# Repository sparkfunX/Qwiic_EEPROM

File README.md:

Qwiic EEPROM - 512Kbit
=======================================

[*Qwiic EEPROM - 512Kbit (SPX-14764)*](https://www.sparkfun.com/products/14764)

A simple breakout for the 512kbit common I2C EEPROMs.

Repository Contents
-------------------

* **/Hardware** - Eagle design files (.brd, .sch)
* **/Firmware** - EEPROM test sketch

Documentation
------------

* **[SparkFun External EEPROM Arduino Library](https://github.com/sparkfun/SparkFun_External_EEPROM_Arduino_Library)** - Arduino library for the Qwiic EEPROM - 512Kbit
* **[Datasheet CAT24C512](https://www.onsemi.com/pub/Collateral/CAT24C512-D.PDF)** - Datasheet for EEPROM part number 24512A
* **[Datasheet RM24C512C](https://cdn.sparkfun.com/assets/2/c/4/c/0/DS-RM24C512C_082.pdf)** - Datasheet for EEPROM part number 24512C
* **[Reading and Writing Serial EEPROMs](https://learn.sparkfun.com/tutorials/reading-and-writing-serial-eeproms)** - Tutorial  

License Information
-------------------

This product is _**open source**_! 

Please review the LICENSE.md file for license information. 

If you have any questions or concerns on licensing, please contact technical support on our [SparkFun forums](https://forum.sparkfun.com/viewforum.php?f=152).

Distributed as-is; no warranty is given.

- Your friends at SparkFun.

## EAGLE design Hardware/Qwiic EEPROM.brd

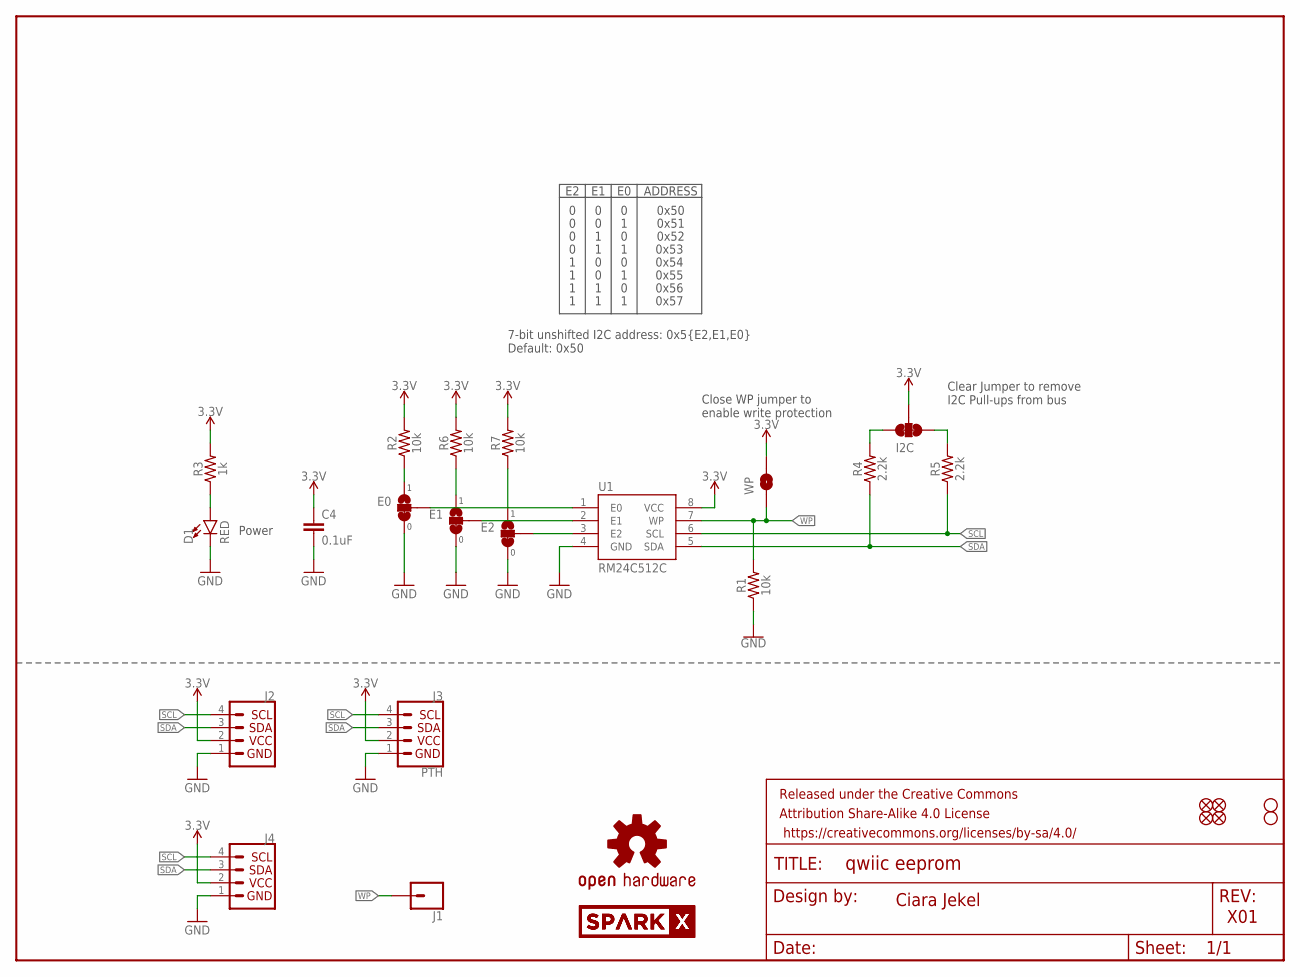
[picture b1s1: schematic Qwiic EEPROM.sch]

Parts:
C4: 0.1uF; 0603
D1: RED; LED-0603
E0, E1, E2: JUMPER-SMT_3_1-NC_TRACE_SILK; SMT-JUMPER_3_1-NC_TRACE_SILK
FRAME1: FRAME-LETTER; CREATIVE_COMMONS
I2C: JUMPER-SMT_3_2-NC_TRACE_SILK; SMT-JUMPER_3_2-NC_TRACE_SILK
J1: CONN_01PTH_NO_SILK_YES_STOP; 1X01_NO_SILK
J2, J4: QWIIC_CONNECTORJS-1MM; 1X04_1MM_RA
J3: PTH; 1X04_NO_SILK
JP1, JP2, JP5, JP6: FIDUCIALUFIDUCIAL; MICRO-FIDUCIAL
JP3, JP4: STAND-OFF
LOGO1: OSHW-LOGOMINI; OSHW-LOGO-MINI
R1, R2, R6, R7: 10k; 0603
R3: 1k; 0603
R4, R5: 2.2k; 0603
U1: RM24C512C; SO08
U$1, U$2: SPARKX-LOGO4; SPARKX-MEDIUM
WP: JUMPER-SMT_2_NO_SILK; SMT-JUMPER_2_NO_SILK

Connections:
3.3V: C4.1, I2C.2, J2.2, J3.2 (VCC), J4.2, R2.2, R3.2, R6.2, R7.2, U1.8 (VCC), WP.2
GND: C4.2, D1.C, E0.3, E1.3, E2.3, J2.1, J3.1 (GND), J4.1, R1.1, U1.4 (GND)
unnamed: I2C.1, R5.2
unnamed: I2C.3, R4.2
unnamed: D1.A, R3.1
unnamed: E2.2, U1.3 (E2)
unnamed: E1.2, U1.2 (E1)
unnamed: E0.2, U1.1 (E0)
unnamed: E0.1, R2.1
unnamed: E2.1, R7.1
unnamed: E1.1, R6.1
SCL: J2.4, J3.4 (SCL), J4.4, R5.1, U1.6 (SCL)
SDA: J2.3, J3.3 (SDA), J4.3, R4.1, U1.5 (SDA)
WP: J1.1, R1.2, U1.7 (WP), WP.1

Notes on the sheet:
Ciara Jekel
X01
7-bit unshifted I2C address: 0x5{E2,E1,E0} Default: 0x50
Clear Jumper to remove I2C Pull-ups from bus
Power
Close WP jumper to enable write protection
ADDRESS
0x50
0x51
0x52
0x53
0x54
0x55
0x56
0x57

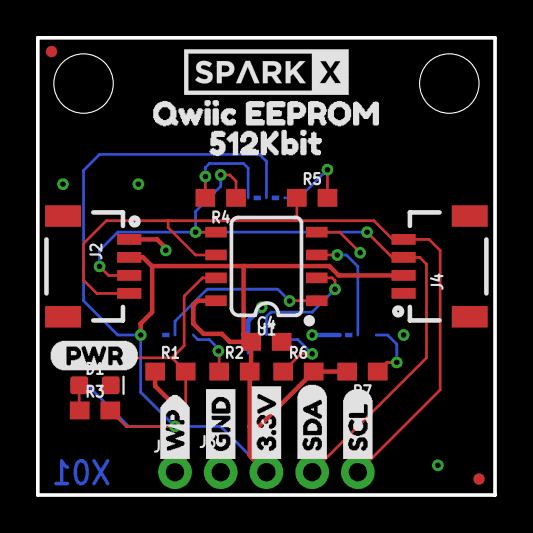
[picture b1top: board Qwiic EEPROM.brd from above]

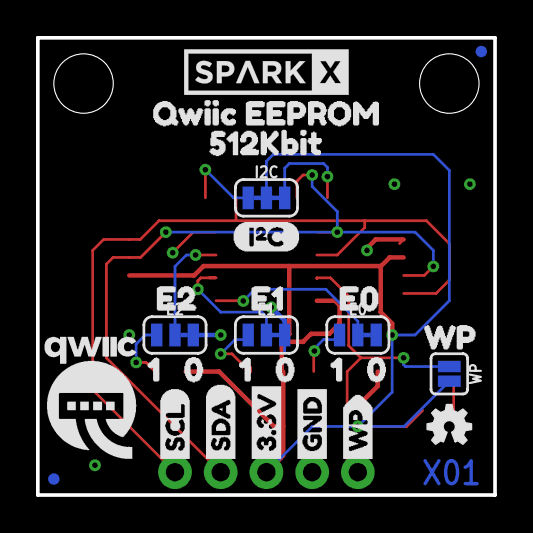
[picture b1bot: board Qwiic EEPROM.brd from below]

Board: 2 copper layers, 25.4 x 25.4 mm, 56 parts (28 on the bottom side), 14 nets.

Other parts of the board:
U$3, U$22: GND1
U$4, U$21: 3#3V2
U$5, U$27: SDA8
U$6, U$26: SCL9
U$7: WP6
U$8: E05
U$9: E23
U$10: (PWR)
U$11: (I_SUPER2_C)
U$12, U$18, U$19: 00
U$13: E14
U$14, U$17: 512KBIT7
U$15, U$16: QWIIC_EEPROM2
U$20, U$23, U$24: 11
U$25, U$28: WP2
U$29: QWIIC-LOGO-MEDIUM

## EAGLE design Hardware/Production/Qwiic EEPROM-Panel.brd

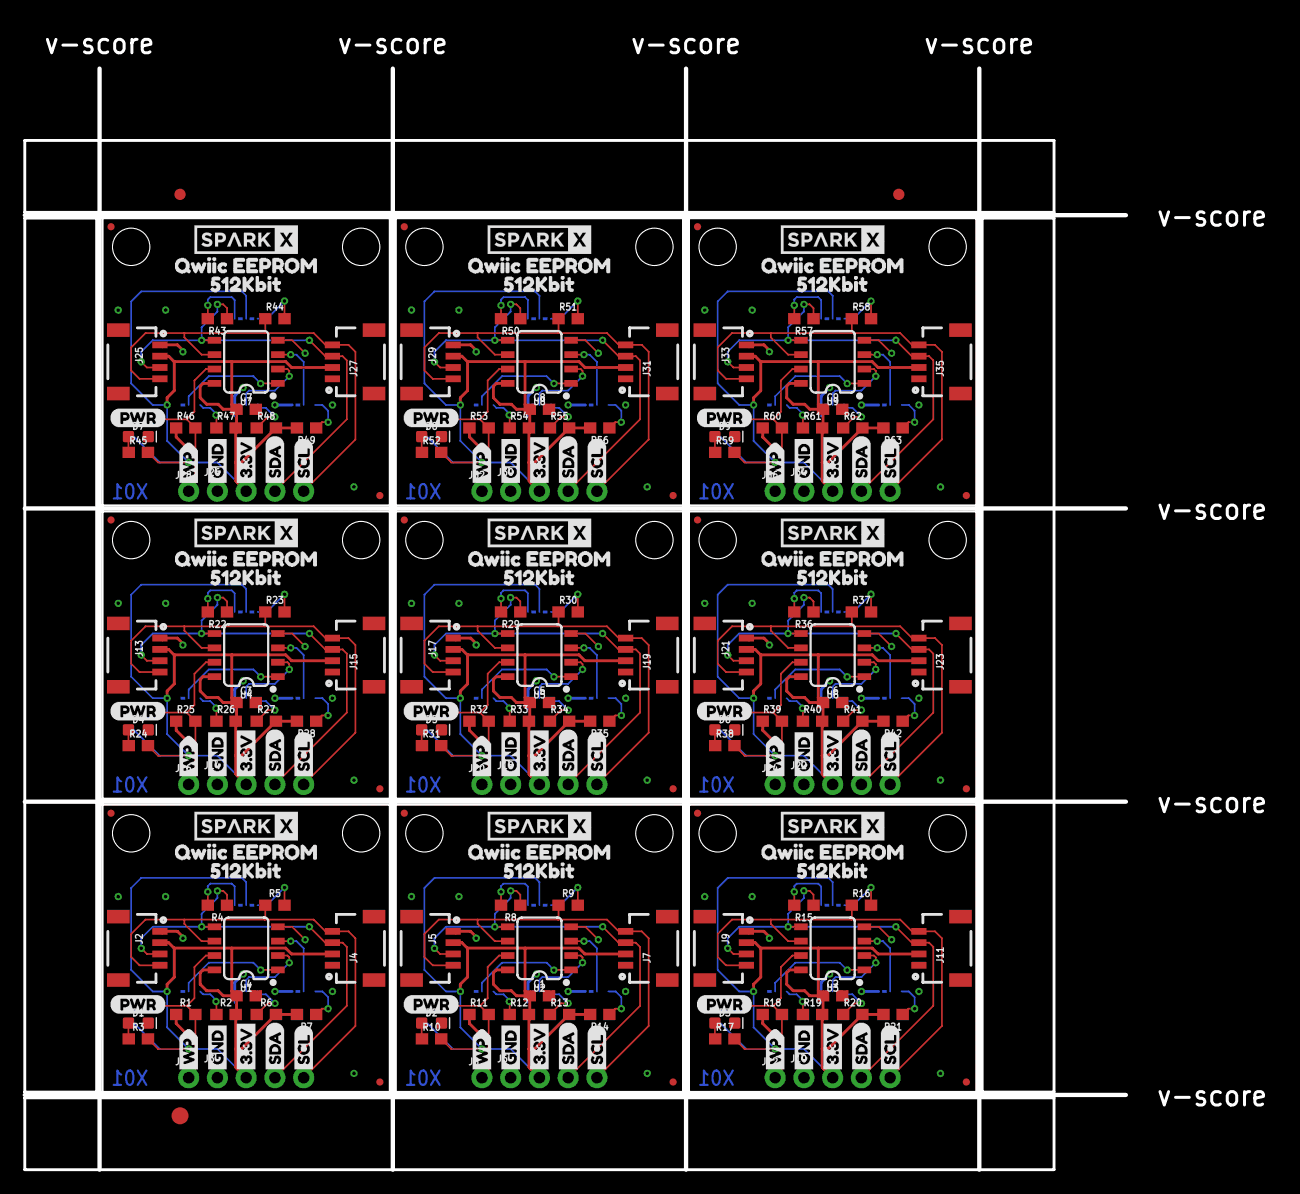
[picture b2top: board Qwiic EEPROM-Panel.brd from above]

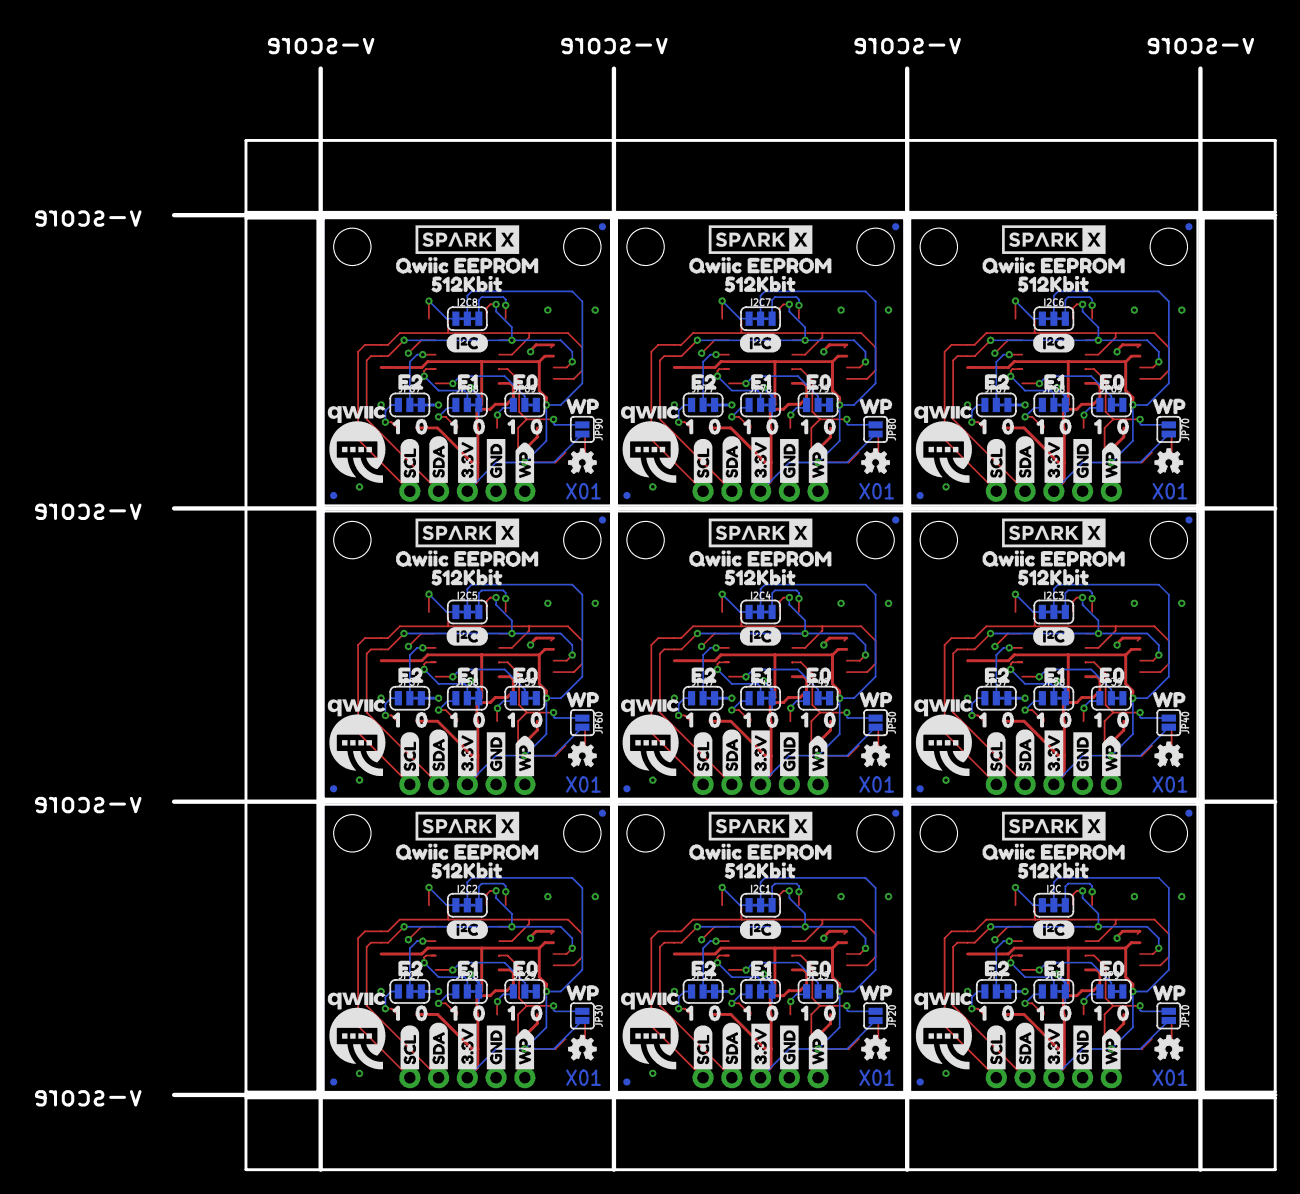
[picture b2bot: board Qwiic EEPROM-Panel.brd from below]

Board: 2 copper layers, 110.5 x 101.2 mm, 498 parts (252 on the bottom side), 126 nets.

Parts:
C1, C2, C3, C4, C5, C6, C7, C8, C9: 0.1uF; 0603
D1, D2, D3, D4, D5, D6, D7, D8, D9: RED; LED-0603
E$1, E$2: FIDUCIAL-1X2
E$3: FIDUCIAL-1.5X3
I2C, I2C1, I2C2, I2C3, I2C4, I2C5, I2C6, I2C7, I2C8: SMT-JUMPER_3_2-NC_TRACE_SILK
J1, J8, J12, J16, J20, J24, J28, J32, J36: 1X01_NO_SILK
J2, J4, J5, J7, J9, J11, J13, J15, J17, J19, J21, J23, J25, J27, J29, J31, J33, J35: SMD; 1X04_1MM_RA
J3, J6, J10, J14, J18, J22, J26, J30, J34: PTH; 1X04_NO_SILK
JP1, JP2, JP5, JP6, JP13, JP14, JP15, JP16, JP23, JP24, JP25, JP26, JP33, JP34, JP35, JP36, JP43, JP44, JP45, JP46, JP53, JP54, JP55, JP56, JP63, JP64, JP65, JP66, JP73, JP74, JP75, JP76, JP83, JP84, JP85, JP86: FIDUCIALUFIDUCIAL; MICRO-FIDUCIAL
JP3, JP4, JP11, JP12, JP21, JP22, JP31, JP32, JP41, JP42, JP51, JP52, JP61, JP62, JP71, JP72, JP81, JP82: STAND-OFF
JP7, JP8, JP9, JP17, JP18, JP19, JP27, JP28, JP29, JP37, JP38, JP39, JP47, JP48, JP49, JP57, JP58, JP59, JP67, JP68, JP69, JP77, JP78, JP79, JP87, JP88, JP89: SMT-JUMPER_3_1-NC_TRACE_SILK
JP10, JP20, JP30, JP40, JP50, JP60, JP70, JP80, JP90: SMT-JUMPER_2_NO_SILK
LOGO1, LOGO2, LOGO3, LOGO4, LOGO5, LOGO6, LOGO7, LOGO8, LOGO9: OSHW-LOGOMINI; OSHW-LOGO-MINI
R1, R2, R6, R7, R11, R12, R13, R14, R18, R19, R20, R21, R25, R26, R27, R28, R32, R33, R34, R35, R39, R40, R41, R42, R46, R47, R48, R49, R53, R54, R55, R56, R60, R61, R62, R63: 10k; 0603
R3, R10, R17, R24, R31, R38, R45, R52, R59: 1k; 0603
R4, R5, R8, R9, R15, R16, R22, R23, R29, R30, R36, R37, R43, R44, R50, R51, R57, R58: 2.2k; 0603
U1, U2, U3, U4, U5, U6, U7, U8, U9: RM24C5; SO08
U$1, U$2, U$30, U$31, U$59, U$60, U$88, U$89, U$117, U$118, U$146, U$147, U$175, U$176, U$204, U$205, U$233, U$234: SPARKX-LOGO4; SPARKX-MEDIUM
U$3, U$22, U$33, U$36, U$62, U$65, U$91, U$94, U$120, U$123, U$149, U$152, U$178, U$181, U$207, U$210, U$236, U$239: GND1
U$4, U$21, U$32, U$37, U$61, U$66, U$90, U$95, U$119, U$124, U$148, U$153, U$177, U$182, U$206, U$211, U$235, U$240: 3#3V2
U$5, U$27, U$35, U$38, U$64, U$67, U$93, U$96, U$122, U$125, U$151, U$154, U$180, U$183, U$209, U$212, U$238, U$241: SDA8
U$6, U$26, U$34, U$39, U$63, U$68, U$92, U$97, U$121, U$126, U$150, U$155, U$179, U$184, U$208, U$213, U$237, U$242: SCL9
U$7, U$42, U$71, U$100, U$129, U$158, U$187, U$216, U$245: WP6
U$8, U$43, U$72, U$101, U$130, U$159, U$188, U$217, U$246: E05
U$9, U$44, U$73, U$102, U$131, U$160, U$189, U$218, U$247: E23
U$10, U$40, U$69, U$98, U$127, U$156, U$185, U$214, U$243: (PWR)
U$11, U$41, U$70, U$99, U$128, U$157, U$186, U$215, U$244: (I_SUPER2_C)
U$12, U$18, U$19, U$50, U$51, U$52, U$79, U$80, U$81, U$108, U$109, U$110, U$137, U$138, U$139, U$166, U$167, U$168, U$195, U$196, U$197, U$224, U$225, U$226, U$253, U$254, U$255: 00
U$13, U$45, U$74, U$103, U$132, U$161, U$190, U$219, U$248: E14
U$14, U$17, U$46, U$49, U$75, U$78, U$104, U$107, U$133, U$136, U$162, U$165, U$191, U$194, U$220, U$223, U$249, U$252: 512KBIT7
U$15, U$16, U$47, U$48, U$76, U$77, U$105, U$106, U$134, U$135, U$163, U$164, U$192, U$193, U$221, U$222, U$250, U$251: QWIIC_EEPROM2
U$20, U$23, U$24, U$53, U$54, U$55, U$82, U$83, U$84, U$111, U$112, U$113, U$140, U$141, U$142, U$169, U$170, U$171, U$198, U$199, U$200, U$227, U$228, U$229, U$256, U$257, U$258: 11
U$25, U$28, U$56, U$57, U$85, U$86, U$114, U$115, U$143, U$144, U$172, U$173, U$201, U$202, U$230, U$231, U$259, U$260: WP2
U$29, U$58, U$87, U$116, U$145, U$174, U$203, U$232, U$261: QWIIC-LOGO-MEDIUM

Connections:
3.3V: C4.1, I2C.2, J2.2, J3.2, J4.2, JP10.2, R2.2, R3.2, R6.2, R7.2, U1.8
3.3V1: C1.1, I2C1.2, J5.2, J6.2, J7.2, JP20.2, R10.2, R12.2, R13.2, R14.2, U2.8
3.3V2: C2.1, I2C2.2, J9.2, J10.2, J11.2, JP30.2, R17.2, R19.2, R20.2, R21.2, U3.8
3.3V3: C3.1, I2C3.2, J13.2, J14.2, J15.2, JP40.2, R24.2, R26.2, R27.2, R28.2, U4.8
3.3V4: C5.1, I2C4.2, J17.2, J18.2, J19.2, JP50.2, R31.2, R33.2, R34.2, R35.2, U5.8
3.3V5: C6.1, I2C5.2, J21.2, J22.2, J23.2, JP60.2, R38.2, R40.2, R41.2, R42.2, U6.8
3.3V6: C7.1, I2C6.2, J25.2, J26.2, J27.2, JP70.2, R45.2, R47.2, R48.2, R49.2, U7.8
3.3V7: C8.1, I2C7.2, J29.2, J30.2, J31.2, JP80.2, R52.2, R54.2, R55.2, R56.2, U8.8
3.3V8: C9.1, I2C8.2, J33.2, J34.2, J35.2, JP90.2, R59.2, R61.2, R62.2, R63.2, U9.8
GND: C4.2, D1.C, J2.1, J3.1, J4.1, JP7.3, JP8.3, JP9.3, R1.1, U1.4
GND1: C1.2, D2.C, J5.1, J6.1, J7.1, JP17.3, JP18.3, JP19.3, R11.1, U2.4
GND2: C2.2, D3.C, J9.1, J10.1, J11.1, JP27.3, JP28.3, JP29.3, R18.1, U3.4
GND3: C3.2, D4.C, J13.1, J14.1, J15.1, JP37.3, JP38.3, JP39.3, R25.1, U4.4
GND4: C5.2, D5.C, J17.1, J18.1, J19.1, JP47.3, JP48.3, JP49.3, R32.1, U5.4
GND5: C6.2, D6.C, J21.1, J22.1, J23.1, JP57.3, JP58.3, JP59.3, R39.1, U6.4
GND6: C7.2, D7.C, J25.1, J26.1, J27.1, JP67.3, JP68.3, JP69.3, R46.1, U7.4
GND7: C8.2, D8.C, J29.1, J30.1, J31.1, JP77.3, JP78.3, JP79.3, R53.1, U8.4
GND8: C9.2, D9.C, J33.1, J34.1, J35.1, JP87.3, JP88.3, JP89.3, R60.1, U9.4
unnamed: I2C.1, R5.2
unnamed: I2C.3, R4.2
unnamed: D1.A, R3.1
unnamed: JP7.2, U1.3
unnamed: JP8.2, U1.2
unnamed: JP9.2, U1.1
unnamed: JP9.1, R2.1
unnamed: JP7.1, R7.1
unnamed: JP8.1, R6.1
unnamed: I2C1.1, R9.2
unnamed: I2C1.3, R8.2
unnamed: D2.A, R10.1
unnamed: JP17.2, U2.3
unnamed: JP18.2, U2.2
unnamed: JP19.2, U2.1
unnamed: JP19.1, R12.1
unnamed: JP17.1, R14.1
unnamed: JP18.1, R13.1
unnamed: I2C2.1, R16.2
unnamed: I2C2.3, R15.2
unnamed: D3.A, R17.1
unnamed: JP27.2, U3.3
unnamed: JP28.2, U3.2
unnamed: JP29.2, U3.1
unnamed: JP29.1, R19.1
unnamed: JP27.1, R21.1
unnamed: JP28.1, R20.1
unnamed: I2C3.1, R23.2
unnamed: I2C3.3, R22.2
unnamed: D4.A, R24.1
unnamed: JP37.2, U4.3
unnamed: JP38.2, U4.2
unnamed: JP39.2, U4.1
unnamed: JP39.1, R26.1
unnamed: JP37.1, R28.1
unnamed: JP38.1, R27.1
unnamed: I2C4.1, R30.2
unnamed: I2C4.3, R29.2
unnamed: D5.A, R31.1
unnamed: JP47.2, U5.3
unnamed: JP48.2, U5.2
unnamed: JP49.2, U5.1
unnamed: JP49.1, R33.1
unnamed: JP47.1, R35.1
unnamed: JP48.1, R34.1
unnamed: I2C5.1, R37.2
unnamed: I2C5.3, R36.2
unnamed: D6.A, R38.1
unnamed: JP57.2, U6.3
unnamed: JP58.2, U6.2
unnamed: JP59.2, U6.1
unnamed: JP59.1, R40.1
unnamed: JP57.1, R42.1
unnamed: JP58.1, R41.1
unnamed: I2C6.1, R44.2
unnamed: I2C6.3, R43.2
unnamed: D7.A, R45.1
unnamed: JP67.2, U7.3
unnamed: JP68.2, U7.2
unnamed: JP69.2, U7.1
unnamed: JP69.1, R47.1
unnamed: JP67.1, R49.1
unnamed: JP68.1, R48.1
unnamed: I2C7.1, R51.2
unnamed: I2C7.3, R50.2
unnamed: D8.A, R52.1
unnamed: JP77.2, U8.3
unnamed: JP78.2, U8.2
unnamed: JP79.2, U8.1
unnamed: JP79.1, R54.1
unnamed: JP77.1, R56.1
unnamed: JP78.1, R55.1
unnamed: I2C8.1, R58.2
unnamed: I2C8.3, R57.2
unnamed: D9.A, R59.1
unnamed: JP87.2, U9.3
unnamed: JP88.2, U9.2
unnamed: JP89.2, U9.1
unnamed: JP89.1, R61.1
unnamed: JP87.1, R63.1
unnamed: JP88.1, R62.1
SCL: J2.4, J3.4, J4.4, R5.1, U1.6
SCL1: J5.4, J6.4, J7.4, R9.1, U2.6
SCL2: J9.4, J10.4, J11.4, R16.1, U3.6
SCL3: J13.4, J14.4, J15.4, R23.1, U4.6
SCL4: J17.4, J18.4, J19.4, R30.1, U5.6
SCL5: J21.4, J22.4, J23.4, R37.1, U6.6
SCL6: J25.4, J26.4, J27.4, R44.1, U7.6
SCL7: J29.4, J30.4, J31.4, R51.1, U8.6
SCL8: J33.4, J34.4, J35.4, R58.1, U9.6
SDA: J2.3, J3.3, J4.3, R4.1, U1.5
SDA1: J5.3, J6.3, J7.3, R8.1, U2.5
SDA2: J9.3, J10.3, J11.3, R15.1, U3.5
SDA3: J13.3, J14.3, J15.3, R22.1, U4.5
SDA4: J17.3, J18.3, J19.3, R29.1, U5.5
SDA5: J21.3, J22.3, J23.3, R36.1, U6.5
SDA6: J25.3, J26.3, J27.3, R43.1, U7.5
SDA7: J29.3, J30.3, J31.3, R50.1, U8.5
SDA8: J33.3, J34.3, J35.3, R57.1, U9.5
WP: J1.1, JP10.1, R1.2, U1.7
WP1: J8.1, JP20.1, R11.2, U2.7
WP2: J12.1, JP30.1, R18.2, U3.7
WP3: J16.1, JP40.1, R25.2, U4.7
WP4: J20.1, JP50.1, R32.2, U5.7
WP5: J24.1, JP60.1, R39.2, U6.7
WP6: J28.1, JP70.1, R46.2, U7.7
WP7: J32.1, JP80.1, R53.2, U8.7
WP8: J36.1, JP90.1, R60.2, U9.7

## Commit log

2018-05-30 added address chart to schematic
2018-06-13 documentation
2018-07-10 add issue template
2020-02-18 Add a test sketch

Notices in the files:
parts and their libraries:
SparkFun-Resistors: Licensing: Creative Commons ShareAlike 4.0 International - https://creativecommons.org/licenses/by-sa/4.0
SparkFun-Aesthetics: Released under the Creative Commons Attribution Share-Alike 4.0 License
SparkFun-Aesthetics: https://creativecommons.org/licenses/by-sa/4.0
